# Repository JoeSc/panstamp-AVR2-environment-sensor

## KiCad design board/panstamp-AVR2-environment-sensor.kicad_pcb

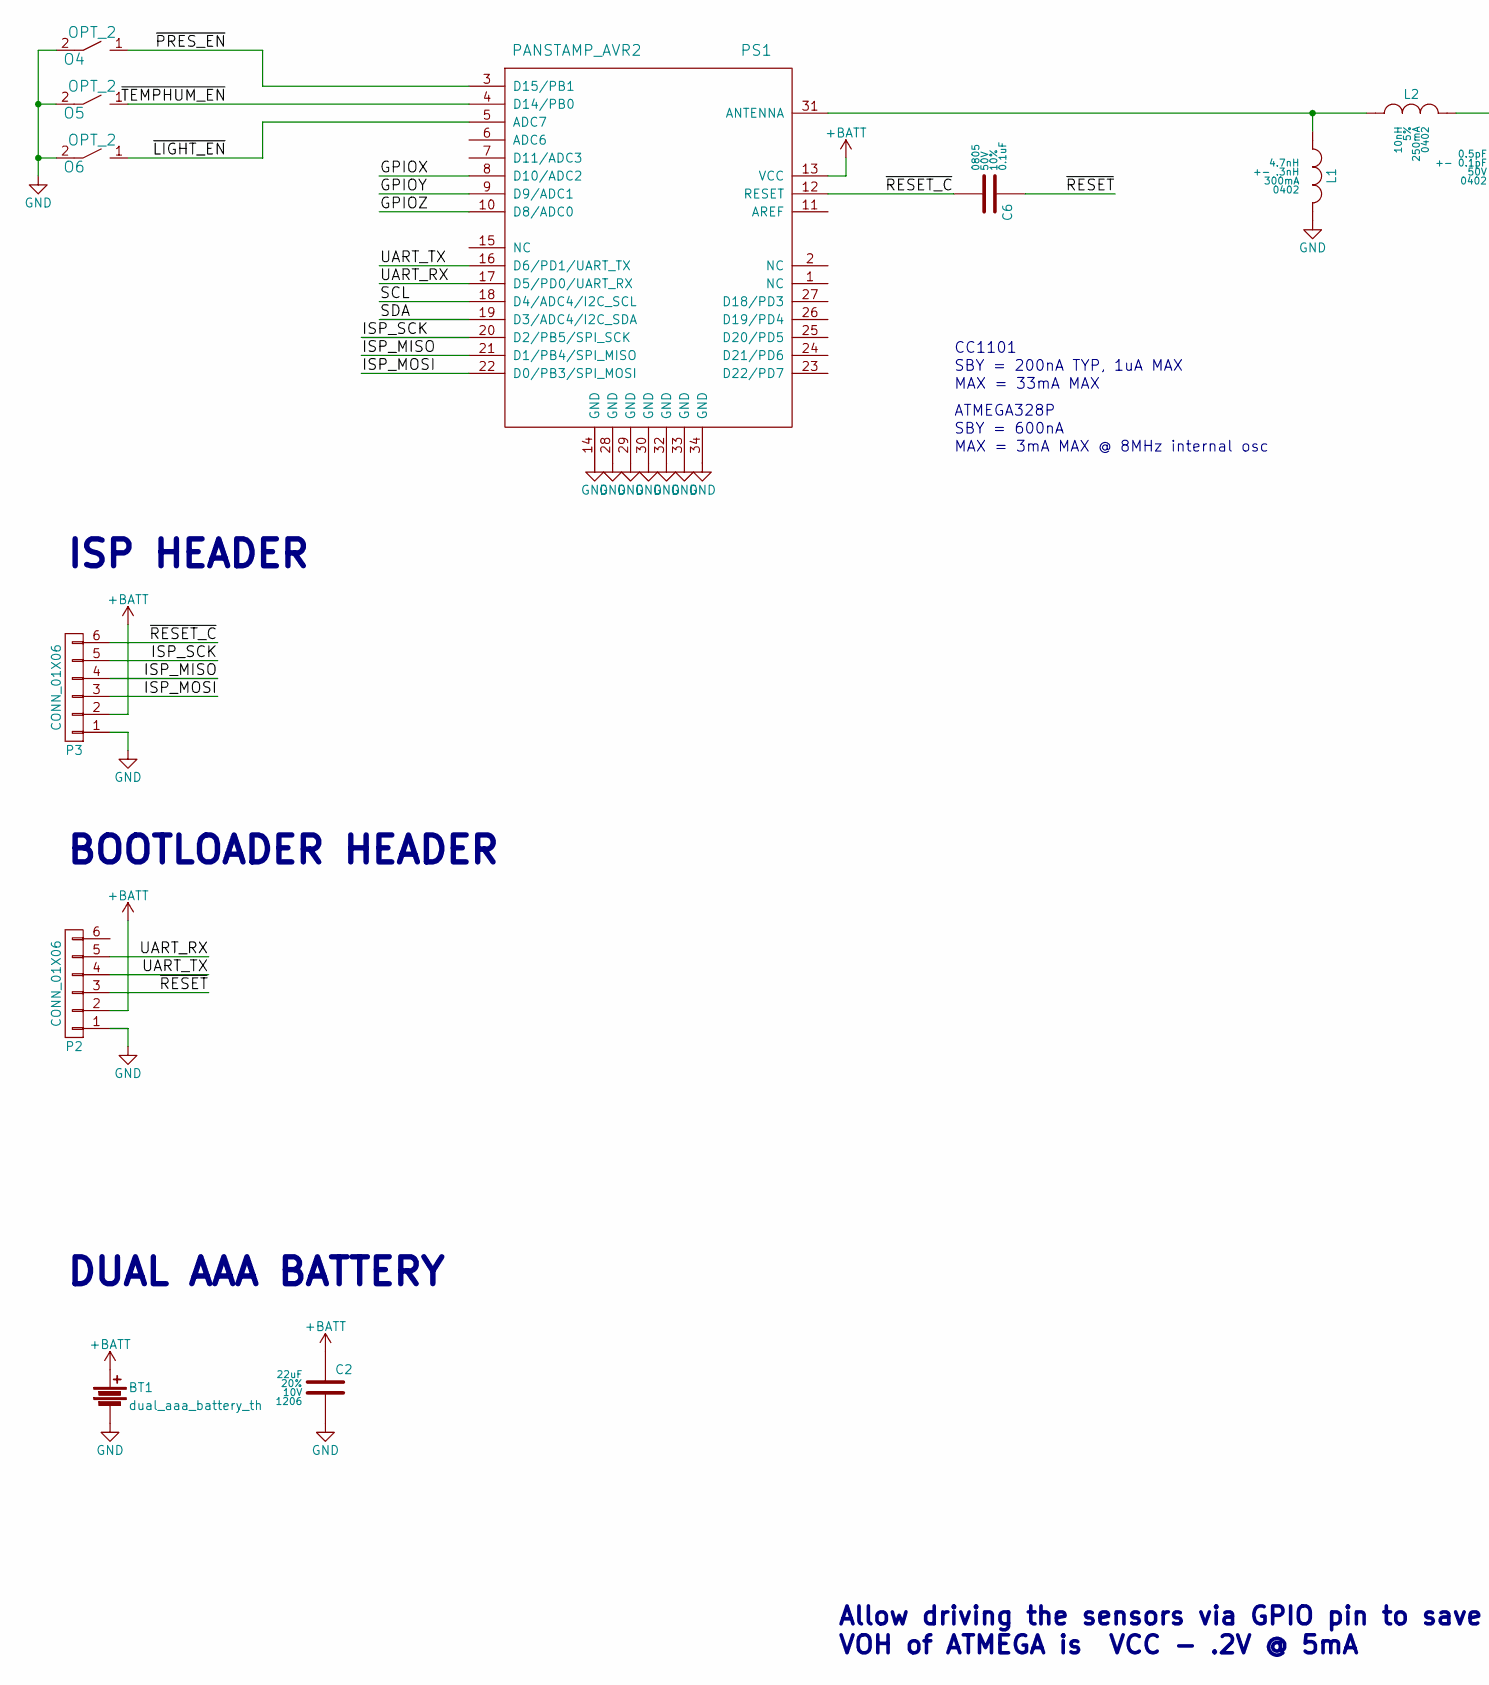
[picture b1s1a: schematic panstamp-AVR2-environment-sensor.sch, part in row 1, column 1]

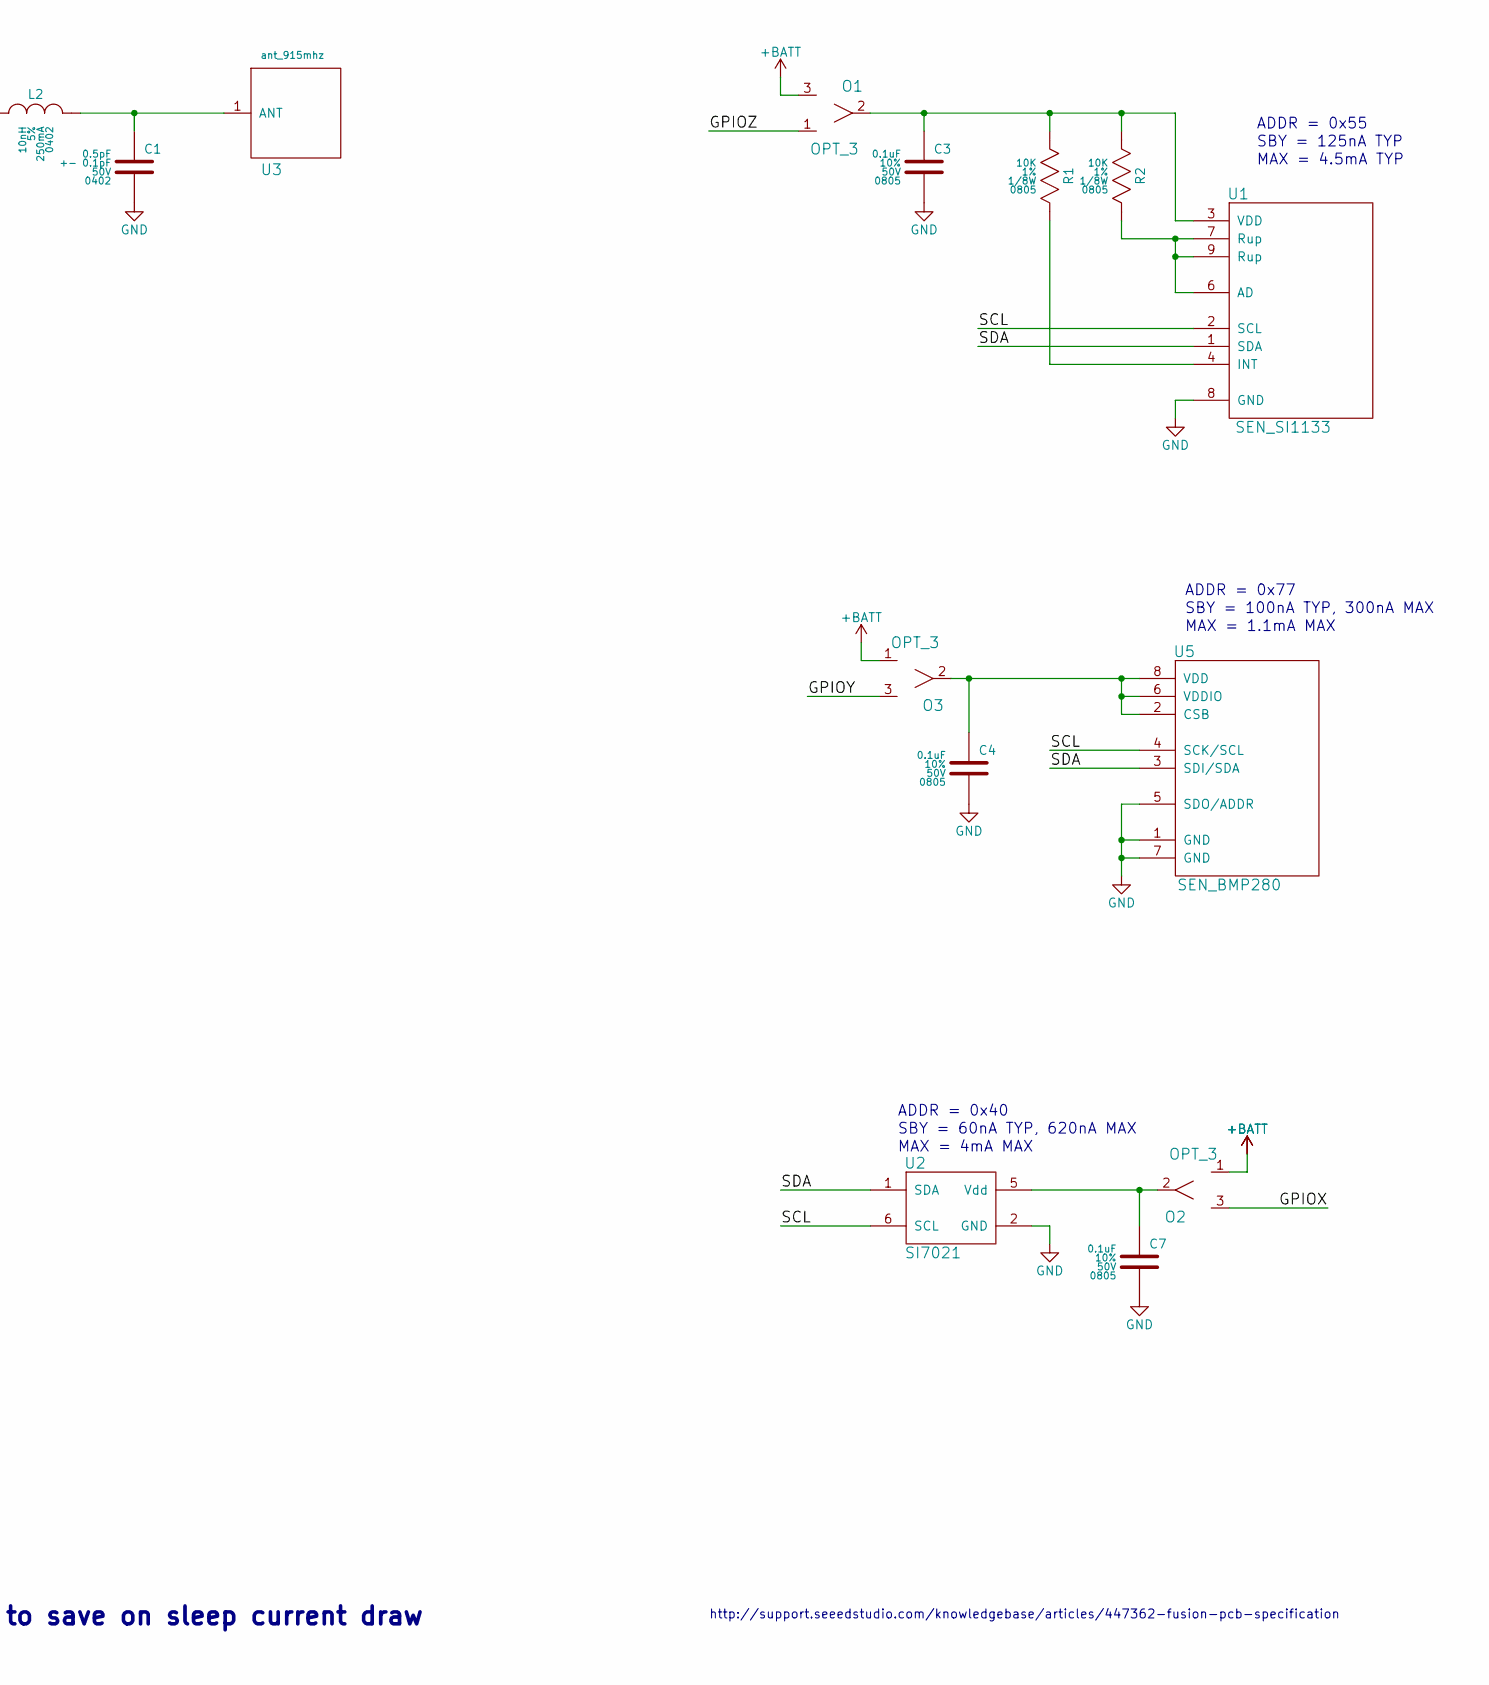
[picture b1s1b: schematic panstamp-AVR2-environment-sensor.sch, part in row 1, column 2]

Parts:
BT1: dual_aaa_battery_th
C1: cap_0p5pf_0p1pf_50v_np0_0402; C_0402; Voltage 50V
C2: cap_22uf_20p_10v_x5r_1206; C_1206; Voltage 10V
C3, C4, C6, C7: cap_0p1uf_10p_50v_x7r_0805; C_0805; Voltage 50V
L1: ind_4p7nh_300ma_0402; R_0402
L2: ind_10nh_250ma_0402; R_0402
O1, O2, O3: OPT_3; SMT_OPT_3
O4, O5, O6: OPT_2; SMT_OPT_2
P2, P3: CONN_01X06; Pin_Header_Straight_1x06_Pitch2.54mm
PS1: PANSTAMP_AVR2; PANSTAMP_2
R1, R2: res_10k_1p_1v8w_0805; R_0805
U1: SEN_SI1133; 10-DFN-2x2
U2: SI7021; DFN-6
U3: ant_915MHz; ant_0915AT43A0026
U5: SEN_BMP280; 8-LGA-2x2p5

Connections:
+BATT: BT1.1, C2.1, O1.3, O2.1, O3.1, P2.2, P3.2, PS1.13 (VCC)
/GPIOX: O2.3, PS1.8 (D10/ADC2)
/GPIOY: O3.3, PS1.9 (D9/ADC1)
/GPIOZ: O1.1, PS1.10 (D8/ADC0)
/ISP_MISO: P3.4, PS1.21 (D1/PB4/SPI_MISO)
/ISP_MOSI: P3.3, PS1.22 (D0/PB3/SPI_MOSI)
/ISP_SCK: P3.5, PS1.20 (D2/PB5/SPI_SCK)
/SCL: PS1.18 (D4/ADC4/I2C_SCL), U1.2 (SCL), U2.6 (SCL), U5.4 (SCK/SCL)
/SDA: PS1.19 (D3/ADC4/I2C_SDA), U1.1 (SDA), U2.1 (SDA), U5.3 (SDI/SDA)
/UART_RX: P2.5, PS1.17 (D5/PD0/UART_RX)
/UART_TX: P2.4, PS1.16 (D6/PD1/UART_TX)
/~LIGHT_EN: O6.1, PS1.5 (ADC7)
/~PRES_EN: O4.1, PS1.3 (D15/PB1)
/~RESET: C6.1, P2.3
/~RESET_C: C6.2, P3.6, PS1.12 (RESET)
/~TEMPHUM_EN: O5.1, PS1.4 (D14/PB0)
GND: BT1.2, C1.2, C2.2, C3.2, C4.2, C7.2, L1.2, O4.2, O5.2, O6.2, P2.1, P3.1, PS1.14 (GND), PS1.28 (GND), PS1.29 (GND), PS1.30 (GND), PS1.32 (GND), PS1.33 (GND), PS1.34 (GND), U1.8 (GND), U2.2 (GND), U5.1 (GND), U5.5 (SDO/ADDR), U5.7 (GND)
unnamed: C1.1, L2.2, U3.1
unnamed: C3.1, O1.2, R1.1, R2.1, U1.3 (VDD)
unnamed: C4.1, O3.2, U5.2 (CSB), U5.6 (VDDIO), U5.8 (VDD)
unnamed: C7.1, O2.2, U2.5 (Vdd)
unnamed: L1.1, L2.1, PS1.31 (ANTENNA)
unnamed: R1.2, U1.4 (INT)
unnamed: R2.2, U1.6 (AD), U1.7 (Rup), U1.9 (Rup)

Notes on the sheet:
ADDR = 0x40
ADDR = 0x77
MAX = 4.5mA TYP
SBY = 125nA TYP
ADDR = 0x55
MAX = 1.1mA MAX
SBY = 100nA TYP, 300nA MAX
http://support.seeedstudio.com/knowledgebase/articles/447362-fusion-pcb-specification
ISP HEADER
BOOTLOADER HEADER
DUAL AAA BATTERY
SBY = 60nA TYP, 620nA MAX
MAX = 4mA MAX
Allow driving the sensors via GPIO pin to save on sleep current draw VOH of ATMEGA is ~ VCC - .2V @ 5mA
SBY = 200nA TYP, 1uA MAX
MAX = 33mA MAX
CC1101
ATMEGA328P
SBY = 600nA
MAX = 3mA MAX @ 8MHz internal osc

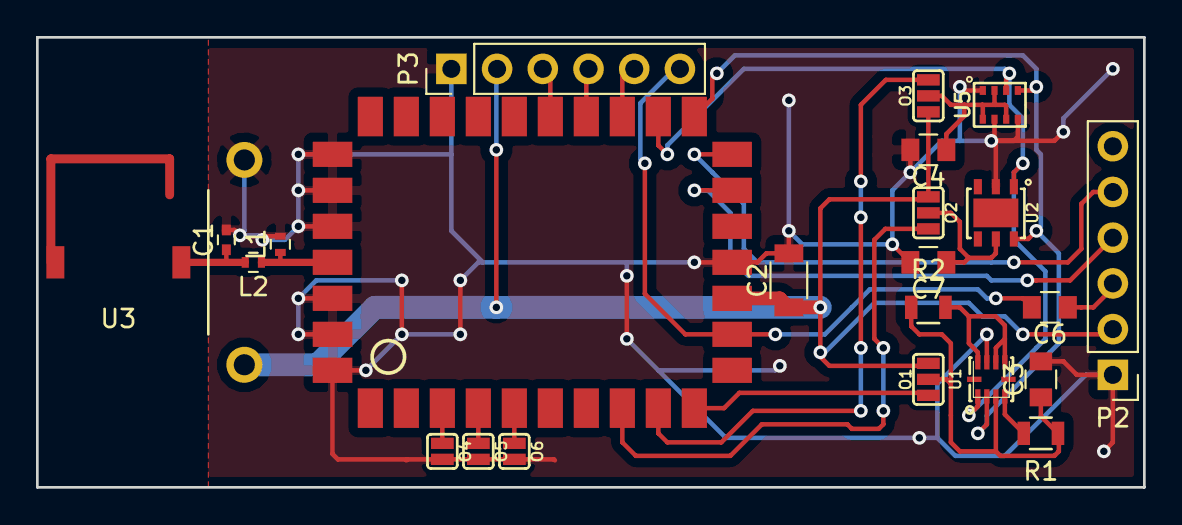
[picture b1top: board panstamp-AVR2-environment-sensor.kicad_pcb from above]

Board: 2 copper layers, 61.5 x 25.0 mm, 24 parts (1 on the bottom side), 24 nets.
